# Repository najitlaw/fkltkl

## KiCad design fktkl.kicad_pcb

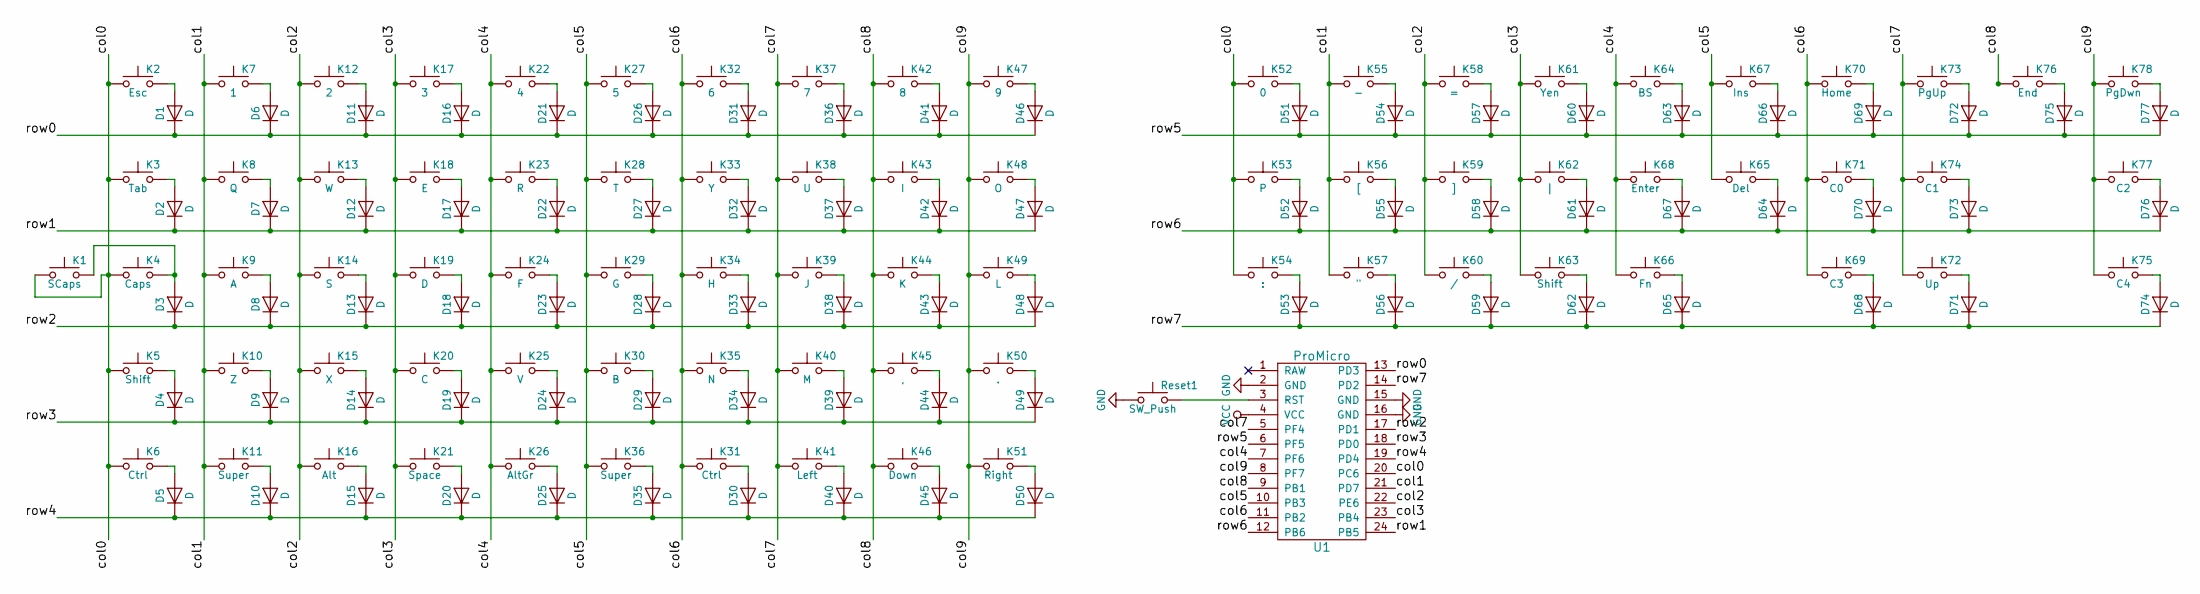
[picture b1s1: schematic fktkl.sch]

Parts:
D1, D2, D3, D4, D5, D6, D7, D8, D9, D10, D11, D12, D13, D14, D15, D16, D17, D18, D19, D20, D21, D22, D23, D24, D25, D26, D27, D28, D29, D30, D31, D32, D33, D34, D35, D36, D37, D38, D39, D40, D41, D42, D43, D44, D45, D46, D47, D48, D49, D50, D51, D52, D53, D54, D55, D56, D57, D58, D59, D60, D61, D62, D63, D64, D65, D66, D67, D68, D69, D70, D71, D72, D73, D74, D75, D76, D77: D; D_SOD123_axial
K1: SCaps; Mx_Alps_125
K2: Esc; Mx_Alps_100
K3: Tab; Mx_Alps_150
K4: Caps; Mx_Alps_175
K5: Shift; Mx_Alps_225
K6, K31: Ctrl; Mx_Alps_150
K7: 1; Mx_Alps_100
K8: Q; Mx_Alps_100
K9: A; Mx_Alps_100
K10: Z; Mx_Alps_100
K11, K36: Super; Mx_Alps_100
K12: 2; Mx_Alps_100
K13: W; Mx_Alps_100
K14: S; Mx_Alps_100
K15: X; Mx_Alps_100
K16: Alt; Mx_Alps_150
K17: 3; Mx_Alps_100
K18: E; Mx_Alps_100
K19: D; Mx_Alps_100
K20: C; Mx_Alps_100
K21: Space; MX-7U-ReversedStabilizers-NoLED
K22: 4; Mx_Alps_100
K23: R; Mx_Alps_100
K24: F; Mx_Alps_100
K25: V; Mx_Alps_100
K26: AltGr; Mx_Alps_150
K27: 5; Mx_Alps_100
K28: T; Mx_Alps_100
K29: G; Mx_Alps_100
K30: B; Mx_Alps_100
K32: 6; Mx_Alps_100
K33: Y; Mx_Alps_100
K34: H; Mx_Alps_100
K35: N; Mx_Alps_100
K37: 7; Mx_Alps_100
K38: U; Mx_Alps_100
K39: J; Mx_Alps_100
K40: M; Mx_Alps_100
K41: Left; Mx_Alps_100
K42: 8; Mx_Alps_100
K43: I; Mx_Alps_100
K44: K; Mx_Alps_100
K45: ,; Mx_Alps_100
K46: Down; Mx_Alps_100
K47: 9; Mx_Alps_100
K48: O; Mx_Alps_100
K49: L; Mx_Alps_100
K50: .; Mx_Alps_100
K51: Right; Mx_Alps_100
K52: 0; Mx_Alps_100
K53: P; Mx_Alps_100
K54: :; Mx_Alps_100
K55: -; Mx_Alps_100
K56: [; Mx_Alps_100
K57: \"; Mx_Alps_100
K58: =; Mx_Alps_100
K59: ]; Mx_Alps_100
K60: /; Mx_Alps_100
K61: Yen; Mx_Alps_100
K62: |; Mx_Alps_150
K63: Shift; Mx_Alps_175
K64: BS; Mx_Alps_100
K65: Del; Mx_Alps_100
K66: Fn; Mx_Alps_100
K67: Ins; Mx_Alps_100
K68: Enter; Mx_Alps_225
K69: C3; Mx_Alps_100
K70: Home; Mx_Alps_100
K71: C0; Mx_Alps_100
K72: Up; Mx_Alps_100
K73: PgUp; Mx_Alps_100
K74: C1; Mx_Alps_100
K75: C4; Mx_Alps_100
K76: End; Mx_Alps_100
K77: C2; Mx_Alps_100
K78: PgDwn; Mx_Alps_100
Reset1: SW_Push; SW_TACT_ALPS_SKQGABE010
U1: ProMicro; Pro_Micro

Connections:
/col0: K1.1, K2.1, K3.1, K4.1, K5.1, K6.1, K52.1, K53.1, K54.1, U1.20 (PC6)
/col1: K7.1, K8.1, K9.1, K10.1, K11.1, K55.1, K56.1, K57.1, U1.21 (PD7)
/col2: K12.1, K13.1, K14.1, K15.1, K16.1, K58.1, K59.1, K60.1, U1.22 (PE6)
/col3: K17.1, K18.1, K19.1, K20.1, K21.1, K61.1, K62.1, K63.1, U1.23 (PB4)
/col4: K22.1, K23.1, K24.1, K25.1, K26.1, K64.1, K66.1, K68.1, U1.7 (PF6); also elsewhere on the board
/col5: K27.1, K28.1, K29.1, K30.1, K36.1, K65.1, K67.1, U1.10 (PB3)
/col6: K31.1, K32.1, K33.1, K34.1, K35.1, K69.1, K70.1, K71.1, U1.11 (PB2)
/col7: K37.1, K38.1, K39.1, K40.1, K41.1, K72.1, K73.1, K74.1, U1.5 (PF4)
/col8: K42.1, K43.1, K44.1, K45.1, K46.1, K76.1, U1.9 (PB1)
/col9: K47.1, K48.1, K49.1, K50.1, K51.1, K75.1, K77.1, K78.1, U1.8 (PF7)
/row0: D1.1 (K), D6.1 (K), D11.1 (K), D16.1 (K), D21.1 (K), D26.1 (K), D31.1 (K), D36.1 (K), D41.1 (K), D46.1 (K), U1.13 (PD3)
/row1: D2.1 (K), D7.1 (K), D12.1 (K), D17.1 (K), D22.1 (K), D27.1 (K), D32.1 (K), D37.1 (K), D42.1 (K), D47.1 (K), U1.24 (PB5)
/row2: D3.1 (K), D8.1 (K), D13.1 (K), D18.1 (K), D23.1 (K), D28.1 (K), D33.1 (K), D38.1 (K), D43.1 (K), D48.1 (K), U1.17 (PD1)
/row3: D4.1 (K), D9.1 (K), D14.1 (K), D19.1 (K), D24.1 (K), D29.1 (K), D34.1 (K), D39.1 (K), D44.1 (K), D49.1 (K), U1.18 (PD0)
/row4: D5.1 (K), D10.1 (K), D15.1 (K), D20.1 (K), D25.1 (K), D30.1 (K), D35.1 (K), D40.1 (K), D45.1 (K), D50.1 (K), U1.19 (PD4)
/row5: D51.1 (K), D54.1 (K), D57.1 (K), D60.1 (K), D63.1 (K), D66.1 (K), D69.1 (K), D72.1 (K), D75.1 (K), D77.1 (K), U1.6 (PF5)
/row6: D52.1 (K), D55.1 (K), D58.1 (K), D61.1 (K), D64.1 (K), D67.1 (K), D70.1 (K), D73.1 (K), D76.1 (K), U1.12 (PB6)
/row7: D53.1 (K), D56.1 (K), D59.1 (K), D62.1 (K), D65.1 (K), D68.1 (K), D71.1 (K), D74.1 (K), U1.14 (PD2)
GND: Reset1.1, U1.2 (GND), U1.15 (GND), U1.16 (GND)
unnamed: D1.2 (A), K2.2
unnamed: D2.2 (A), K3.2
unnamed: D3.2 (A), K1.2, K4.2
unnamed: D4.2 (A), K5.2
unnamed: D5.2 (A), K6.2
unnamed: D6.2 (A), K7.2
unnamed: D7.2 (A), K8.2
unnamed: D8.2 (A), K9.2
unnamed: D9.2 (A), K10.2
unnamed: D10.2 (A), K11.2
unnamed: D11.2 (A), K12.2
unnamed: D12.2 (A), K13.2
unnamed: D13.2 (A), K14.2
unnamed: D14.2 (A), K15.2
unnamed: D15.2 (A), K16.2
unnamed: D16.2 (A), K17.2
unnamed: D17.2 (A), K18.2
unnamed: D18.2 (A), K19.2
unnamed: D19.2 (A), K20.2
unnamed: D20.2 (A), K21.2
unnamed: D21.2 (A), K22.2
unnamed: D22.2 (A), K23.2
unnamed: D23.2 (A), K24.2
unnamed: D24.2 (A), K25.2
unnamed 43: D25.2 (A), K26.2; also elsewhere on the board
unnamed: D26.2 (A), K27.2
unnamed: D27.2 (A), K28.2
unnamed: D28.2 (A), K29.2
unnamed: D29.2 (A), K30.2
unnamed: D30.2 (A), K31.2
unnamed: D31.2 (A), K32.2
unnamed: D32.2 (A), K33.2
unnamed: D33.2 (A), K34.2
unnamed: D34.2 (A), K35.2
unnamed: D35.2 (A), K36.2
unnamed: D36.2 (A), K37.2
unnamed: D37.2 (A), K38.2
unnamed: D38.2 (A), K39.2
unnamed: D39.2 (A), K40.2
unnamed: D40.2 (A), K41.2
unnamed: D41.2 (A), K42.2
unnamed: D42.2 (A), K43.2
unnamed: D43.2 (A), K44.2
unnamed: D44.2 (A), K45.2
unnamed: D45.2 (A), K46.2
unnamed: D46.2 (A), K47.2
unnamed: D47.2 (A), K48.2
unnamed: D48.2 (A), K49.2
unnamed: D49.2 (A), K50.2
unnamed: D50.2 (A), K51.2
unnamed: D51.2 (A), K52.2
unnamed: D52.2 (A), K53.2
unnamed: D53.2 (A), K54.2
unnamed: D54.2 (A), K55.2
unnamed: D55.2 (A), K56.2
unnamed: D56.2 (A), K57.2
unnamed: D57.2 (A), K58.2
unnamed: D58.2 (A), K59.2
unnamed: D59.2 (A), K60.2
unnamed: D60.2 (A), K61.2
unnamed: D61.2 (A), K62.2
unnamed: D62.2 (A), K63.2
unnamed: D63.2 (A), K64.2
unnamed: D64.2 (A), K65.2
unnamed: D65.2 (A), K66.2
unnamed: D66.2 (A), K67.2
unnamed: D67.2 (A), K68.2
unnamed: D68.2 (A), K69.2
unnamed: D69.2 (A), K70.2
unnamed: D70.2 (A), K71.2
unnamed: D71.2 (A), K72.2
unnamed: D72.2 (A), K73.2
unnamed: D73.2 (A), K74.2
unnamed: D74.2 (A), K75.2
unnamed: D75.2 (A), K76.2
unnamed: D76.2 (A), K77.2
unnamed: D77.2 (A), K78.2
unnamed: Reset1.2, U1.3 (RST)
VCC: U1.4 (VCC)

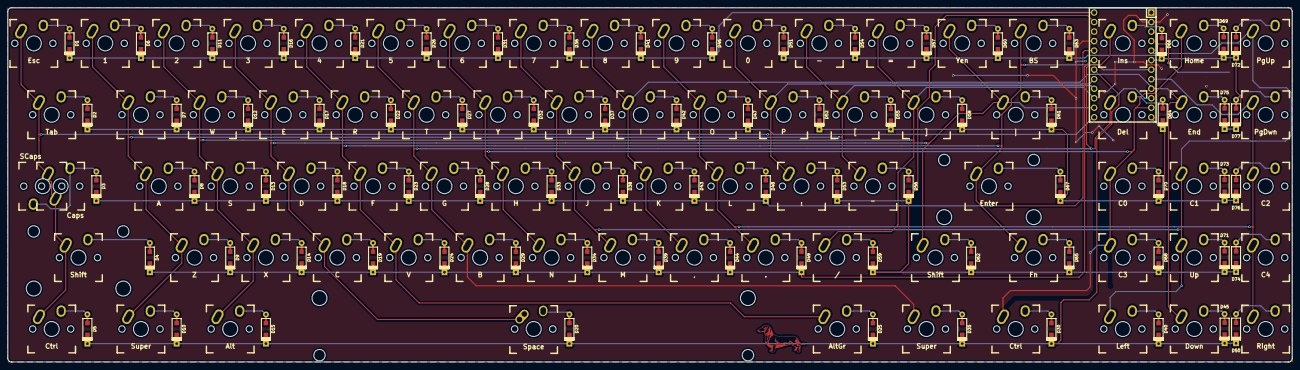
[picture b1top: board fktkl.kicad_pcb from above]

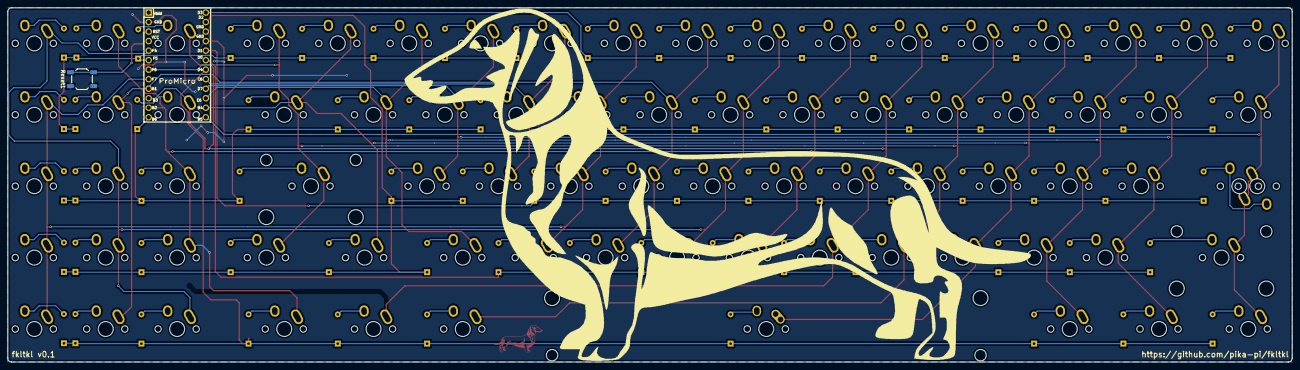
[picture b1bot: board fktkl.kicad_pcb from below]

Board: 2 copper layers, 342.6 x 94.5 mm, 158 parts (2 on the bottom side), 97 nets.

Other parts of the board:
K26#2: AltGr; Mx_Alps_150

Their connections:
/col4: K26#2.1; also elsewhere on the board
unnamed 43: K26#2.2; also elsewhere on the board

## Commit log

2018-05-13 iniital pcb design
2018-05-20 changed controller to pro micro
2018-05-20 removed unused mounting hole
2018-05-20 updated netlist
2018-05-20 added lyout image
2018-05-26 connected row7
2018-06-01 switche left ctrl and left gui
